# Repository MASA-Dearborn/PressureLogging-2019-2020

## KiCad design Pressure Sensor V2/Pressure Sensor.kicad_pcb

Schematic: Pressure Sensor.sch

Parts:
J1: Conn_01x10; 3M_N2510-6V0C-RB-WD
U1, U2, U3: PressureSensor; SMT-NN

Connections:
+3V3: J1.1, J1.8, U1.2, U2.2, U3.2
GND: J1.2, J1.9, U1.1, U2.1, U3.1
MISO: J1.3, U1.3, U2.3, U3.3
SCLK: J1.4, U1.4, U2.4, U3.4
SS0: J1.7, U1.5
SS1: J1.6, U2.5
SS2: J1.5, U3.5

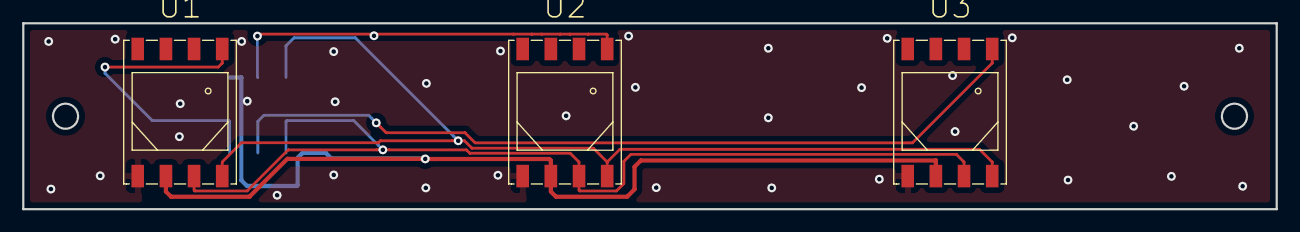
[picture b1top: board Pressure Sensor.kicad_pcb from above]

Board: 2 copper layers, 113.0 x 16.8 mm, 4 parts (1 on the bottom side), 7 nets.

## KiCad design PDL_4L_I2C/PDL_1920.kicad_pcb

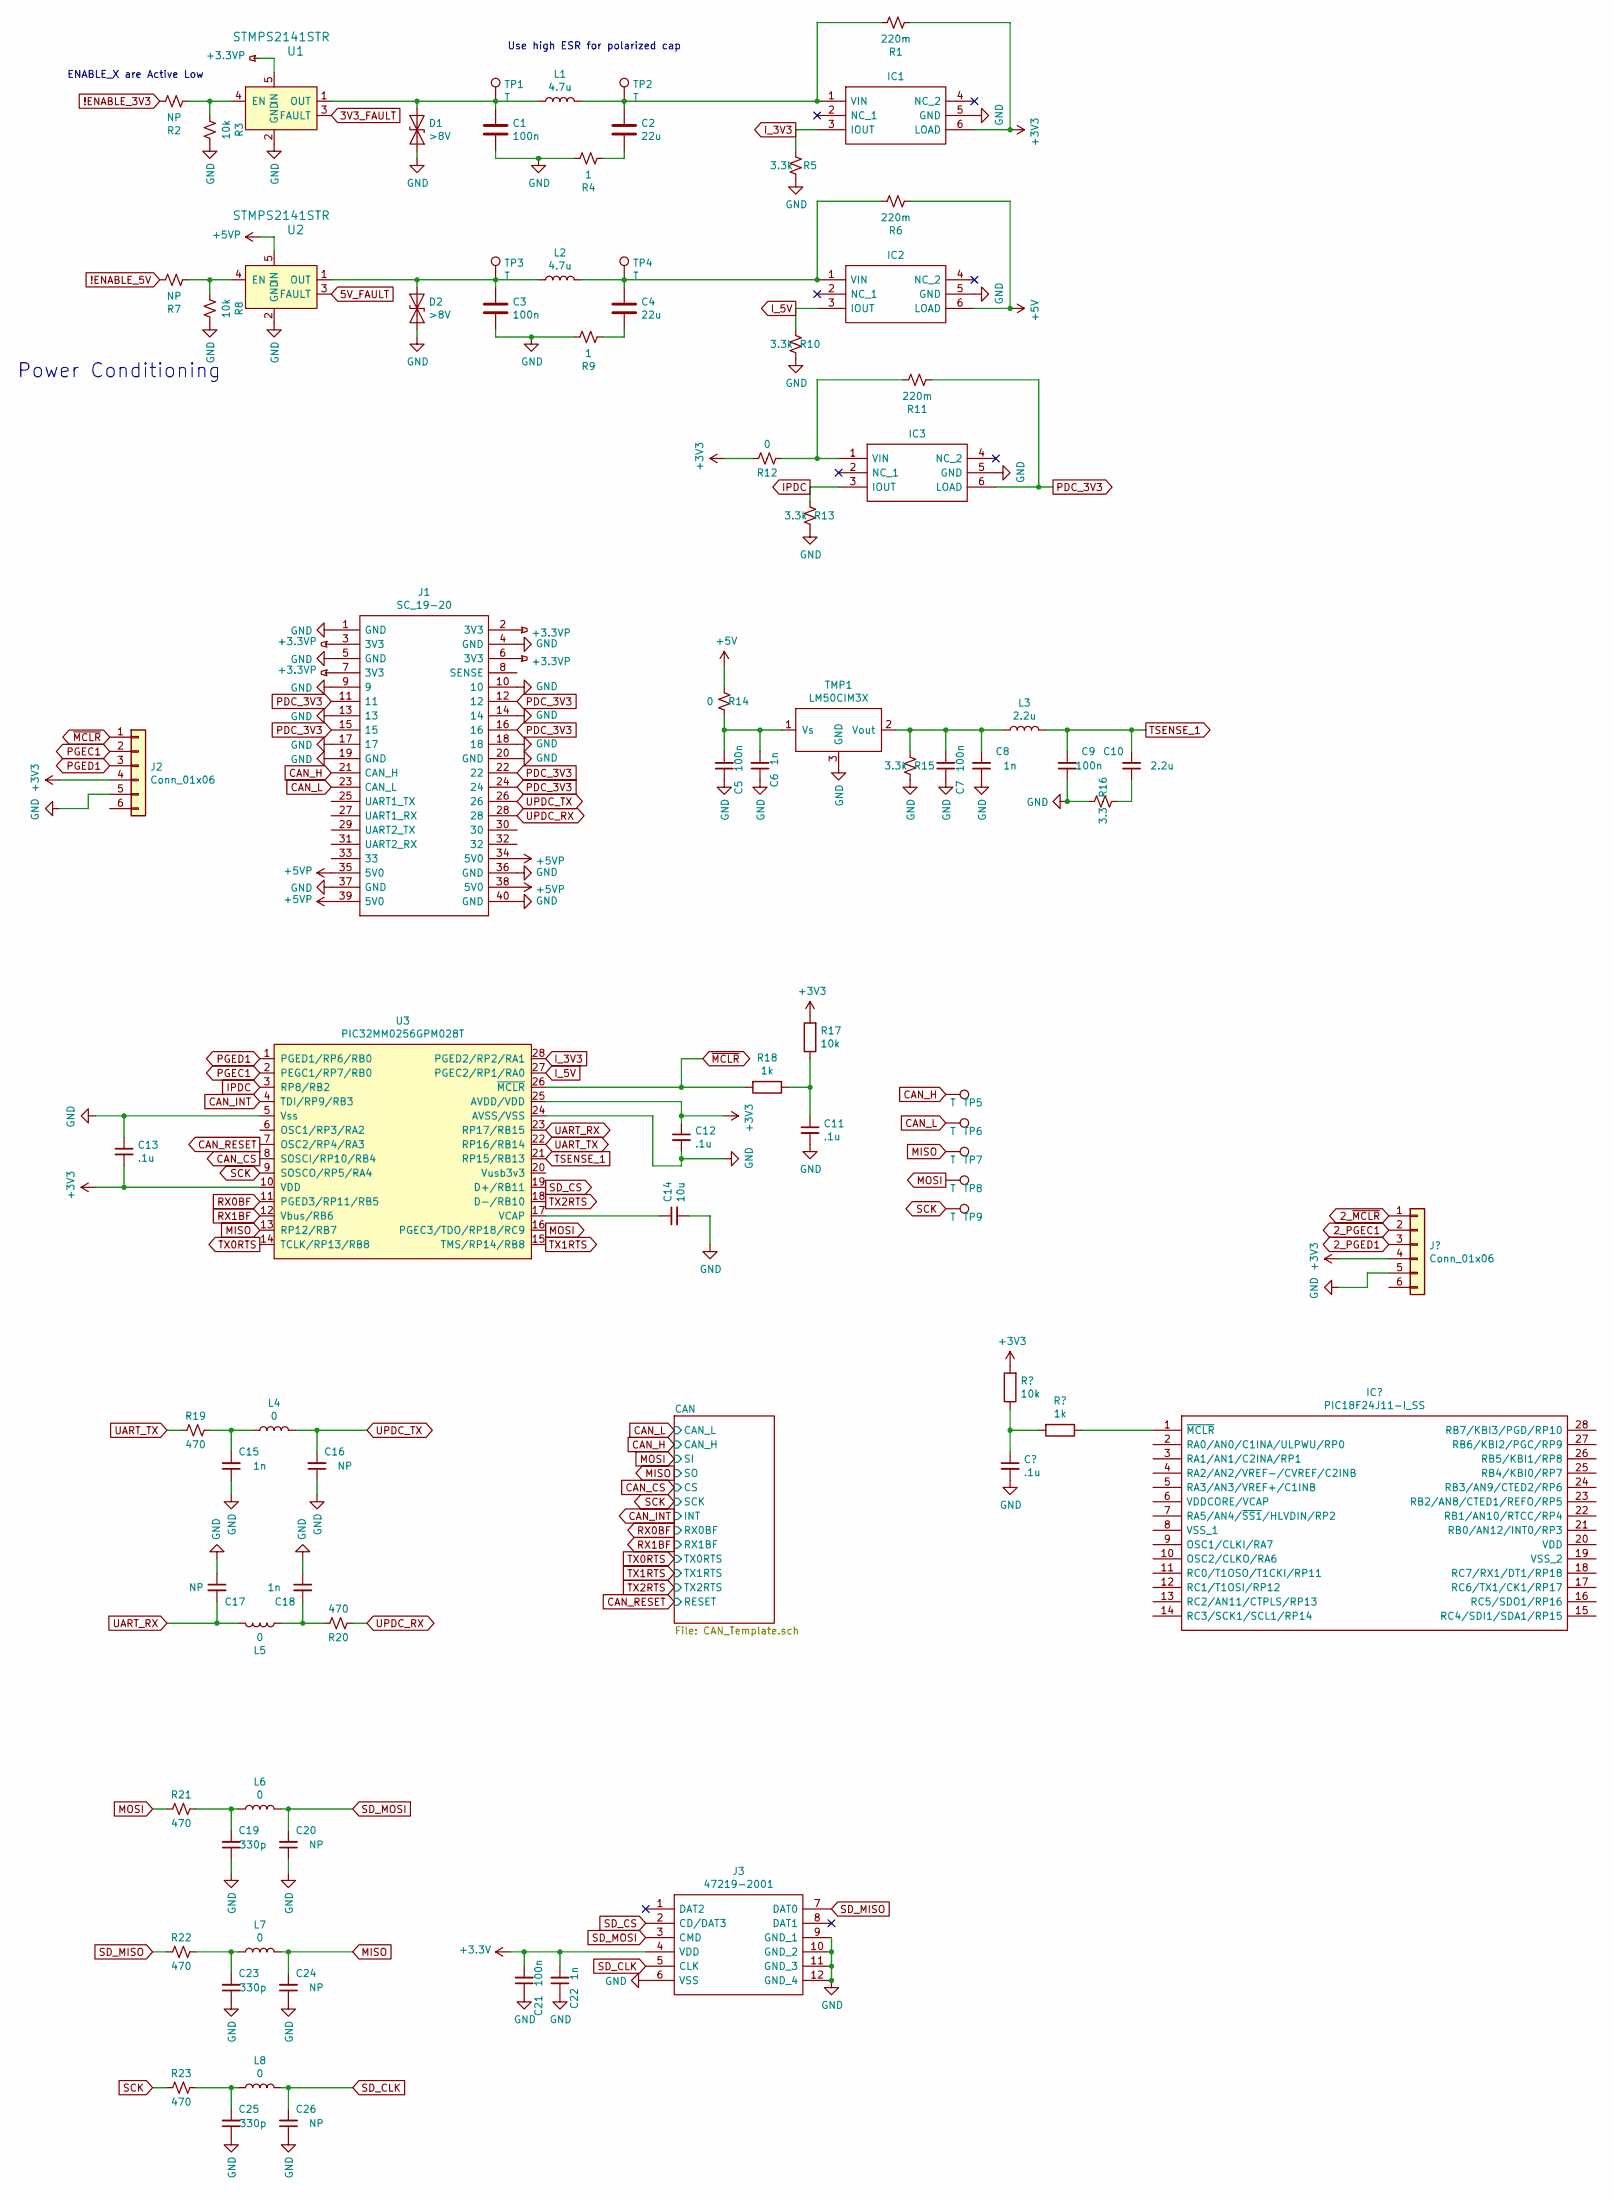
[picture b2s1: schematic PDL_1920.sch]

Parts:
C1, C3, C5, C7, C9, C21: 100n; C_0603_1608Metric
C2, C4: 22u; C_0603_1608Metric
C6, C8, C15, C18, C22: 1n; C_0603_1608Metric
C10: 2.2u; C_0603_1608Metric
C11, C12, C13: .1u; C_0603_1608Metric
C14: 10u; C_0603_1608Metric
C16, C17, C20, C24, C26: NP; C_0603_1608Metric
C19, C23, C25: 330p; C_0603_1608Metric
D1, D2: >8V; D_0805_2012Metric
IC1, IC2, IC3: FAN4010IL6X_F113; UFDFN-6_1.45x1mm; Manufacturer_Part_Number FAN4010IL6X_F113; Mouser Part Number 512-FAN4010IL6X_F113
J1: SC_19-20; Stack_Connector_2019_2020; Manufacturer_Part_Number TFC-120-32-F-D-A-K-TR
J2: Conn_01x06; PinHeader_1x06_P2.54mm_Vertical
J3: 47219-2001; 472192001; Mouser Part Number 538-47219-2001
L1: 4.7u; C_0805_2012Metric; PART# 74438324033; Digi-Key_PN 732-5684-1-ND
L2: 4.7u; L_0805_2012Metric; MPN 74438324033; Digi-Key_PN 732-5684-1-ND
L3: 2.2u; L_0603_1608Metric
L4, L5, L6, L7, L8: 0; L_0603_1608Metric
R1, R6, R11: 220m; R_0805_2012Metric
R2, R7: NP; R_0603_1608Metric
R3, R8, R17: 10k; R_0603_1608Metric
R4, R9: 1; R_0603_1608Metric
R5, R10, R13, R15: 3.3k; R_0603_1608Metric
R12, R14: 0; R_0603_1608Metric
R16: 3.3; R_0603_1608Metric
R18: 1k; R_0603_1608Metric
R19, R20, R21, R22, R23: 470; R_0603_1608Metric
TMP1: LM50CIM3X; SOT-23
TP1, TP2, TP3, TP4, TP5, TP6, TP7, TP8, TP9: T; TP380X203
U1, U2: STMPS2141STR; SOT-753; MPN STMPS2141STR; Digi-Key_PN 497-6933-1-ND
U3: PIC32MM0256GPM028T; PIC32MM0016GPL028EM6

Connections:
3V3_FAULT: U1.3 (FAULT)
5V_FAULT: U2.3 (FAULT)
!ENABLE_3V3: R2.1
!ENABLE_5V: R7.1
+3.3VP: J1.2 (3V3), J1.3 (3V3), J1.6 (3V3), J1.7 (3V3), U1.5 (IN)
+5V: IC2.6 (LOAD), R6.2, R14.2; also elsewhere on the board
+5VP: J1.34 (5V0), J1.35 (5V0), J1.38 (5V0), J1.39 (5V0), U2.5 (IN)
CAN_CS: U3.8 (SOSCI/RP10/RB4); also elsewhere on the board
CAN_H: J1.21 (CAN_H), TP5.1; also elsewhere on the board
CAN_INT: U3.4 (TDI/RP9/RB3); also elsewhere on the board
CAN_L: J1.23 (CAN_L), TP6.1; also elsewhere on the board
CAN_RESET: U3.7 (OSC2/RP4/RA3); also elsewhere on the board
IPDC: IC3.3 (IOUT), R13.2, U3.3 (RP8/RB2)
I_3V3: IC1.3 (IOUT), R5.2, U3.28 (PGED2/RP2/RA1)
I_5V: IC2.3 (IOUT), R10.2, U3.27 (PGEC2/RP1/RA0)
MISO: C24.2, L7.2, TP7.1, U3.13 (RP12/RB7); also elsewhere on the board
MOSI: R21.2, TP8.1, U3.16 (PGEC3/TDO/RP18/RC9); also elsewhere on the board
unnamed: C1.1, D1.2 (A2), L1.1, TP1.1, U1.1 (OUT)
unnamed: C2.1, IC1.1 (VIN), L1.2, R1.1, TP2.1
unnamed: C2.2, R4.2
unnamed: C3.1, D2.2 (A2), L2.1, TP3.1, U2.1 (OUT)
unnamed: C4.1, IC2.1 (VIN), L2.2, R6.1, TP4.1
unnamed: C4.2, R9.2
unnamed: C5.2, C6.2, R14.1, TMP1.1 (Vs)
unnamed: C7.2, C8.2, L3.1, R15.2, TMP1.2 (Vout)
unnamed: C10.1, R16.1
unnamed: C11.1, R17.1, R18.1
unnamed: C14.1, U3.17 (VCAP)
unnamed: C15.2, L4.1, R19.1
unnamed: C18.2, L5.1, R20.1
unnamed: C19.2, L6.1, R21.1
unnamed: C23.2, L7.1, R22.1
unnamed: C25.2, L8.1, R23.1
unnamed: IC3.1 (VIN), R11.1, R12.2
unnamed: R2.2, R3.2, U1.4 (EN)
unnamed: R7.2, R8.2, U2.4 (EN)
PDC_3V3: IC3.6 (LOAD), J1.11, J1.12, J1.15, J1.16, J1.22, J1.24, R11.2
PGEC1: J2.2, U3.2 (PEGC1/RP7/RB0)
PGED1: J2.3, U3.1 (PGED1/RP6/RB0)
RX0BF: U3.11 (PGED3/RP11/RB5); also elsewhere on the board
RX1BF: U3.12 (Vbus/RB6); also elsewhere on the board
SCK: R23.2, TP9.1, U3.9 (SOSCO/RP5/RA4); also elsewhere on the board
SD_CLK: C26.2, J3.5 (CLK), L8.2
SD_CS: J3.2 (CD/DAT3), U3.19 (D+/RB11)
SD_MISO: J3.7 (DAT0), R22.2
SD_MOSI: C20.2, J3.3 (CMD), L6.2
TSENSE_1: C9.2, C10.2, L3.2, U3.21 (RP15/RB13)
TX0RTS: U3.14 (TCLK/RP13/RB8); also elsewhere on the board
TX1RTS: U3.15 (TMS/RP14/RB8); also elsewhere on the board
TX2RTS: U3.18 (D-/RB10); also elsewhere on the board
UART_RX: C17.2, L5.2, U3.23 (RP17/RB15)
UART_TX: R19.2, U3.22 (RP16/RB14)
UPDC_RX: J1.28, R20.2
UPDC_TX: C16.2, J1.26, L4.2
~MCLR: J2.1, R18.2, U3.26 (~MCLR)

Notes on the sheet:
Use high ESR for polarized cap
ENABLE_X are Active Low
Power Conditioning

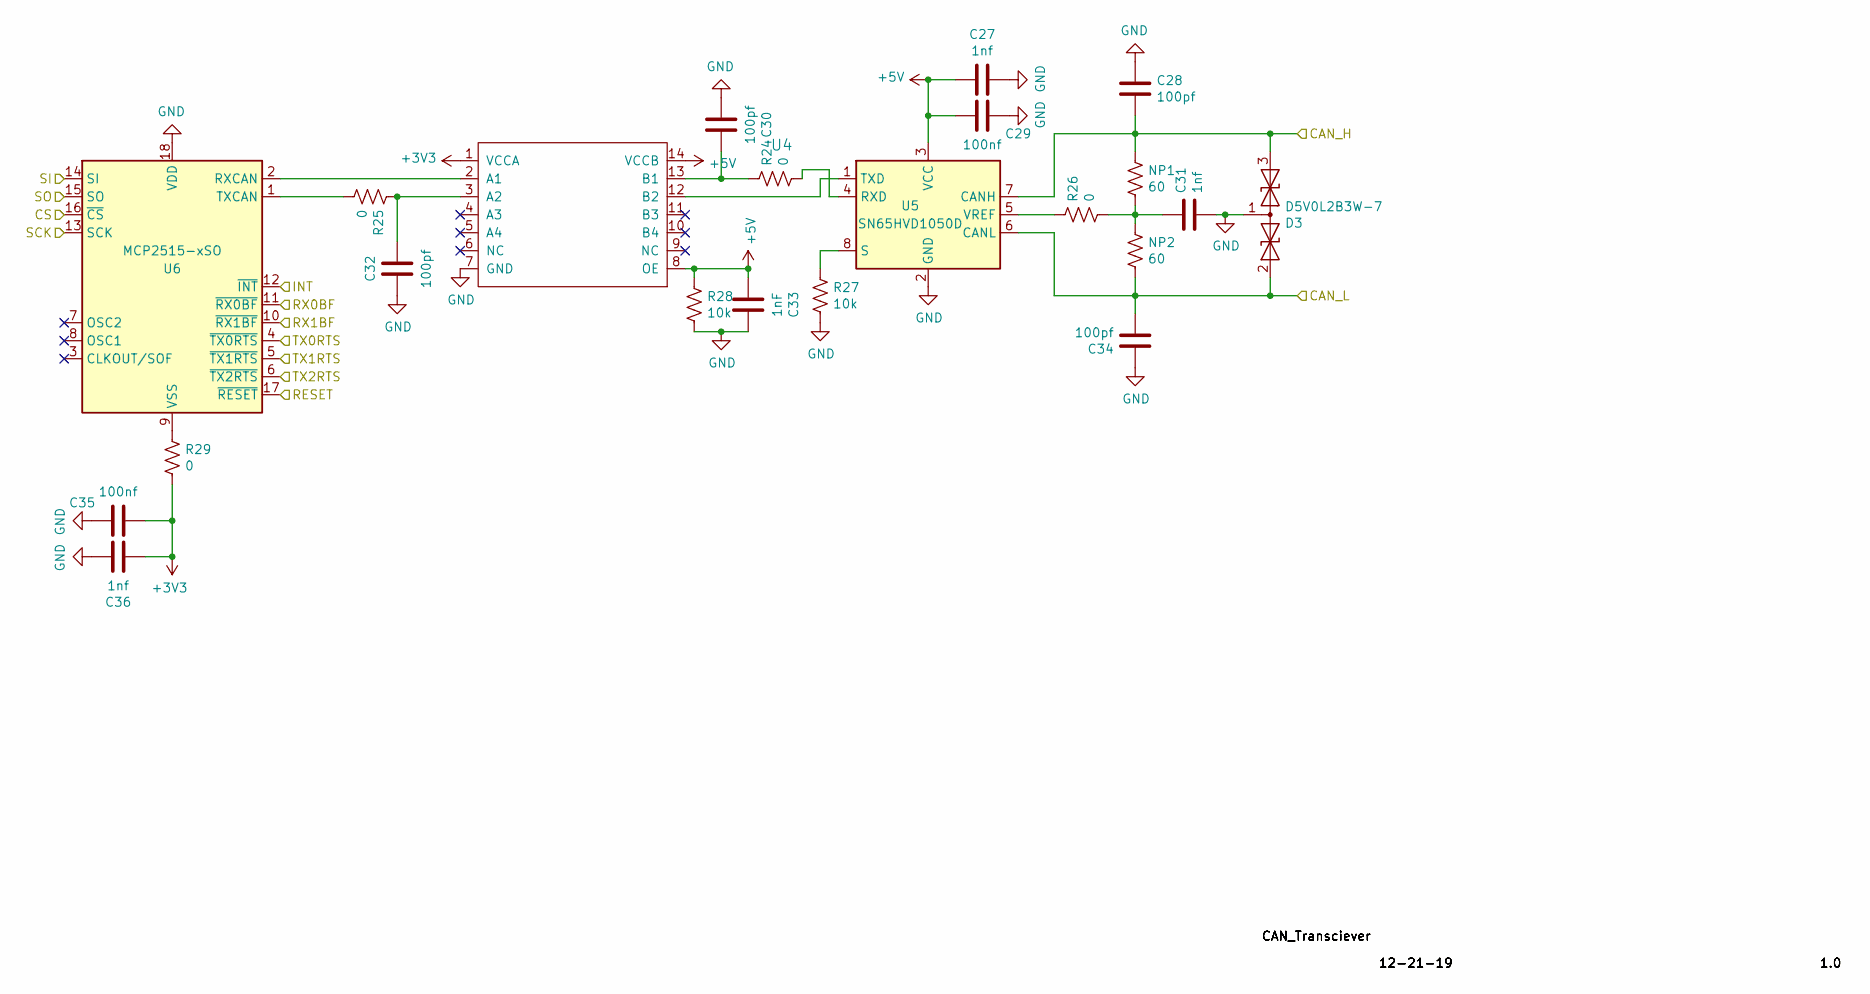
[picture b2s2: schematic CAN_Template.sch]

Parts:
C27, C31, C36: 1nf; C_0603_1608Metric
C28, C30, C32, C34: 100pf; C_0603_1608Metric
C29, C35: 100nf; C_0603_1608Metric
C33: 1nF; C_0603_1608Metric
D3: D5V0L2B3W-7; SOT-23
NP1, NP2: 60; R_0603_1608Metric
R24, R25, R26, R29: 0; R_0603_1608Metric
R27, R28: 10k; R_0603_1608Metric
U4: TXB0104PWR
U5: SN65HVD1050D; SOIC-8_3.9x4.9mm_P1.27mm
U6: MCP2515-xSO; SOIC-18W_7.5x11.6mm_P1.27mm

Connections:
+5V: C27.2, C29.1, C33.2, R28.1, U4.8 (OE), U4.14 (VCCB), U5.3 (VCC); also elsewhere on the board
CAN_CS: U6.16 (~CS); also elsewhere on the board
CAN_H: C28.2, D3.3 (A2), NP1.1, U5.7 (CANH); also elsewhere on the board
CAN_INT: U6.12 (~INT); also elsewhere on the board
CAN_L: C34.2, D3.2 (A1), NP2.2, U5.6 (CANL); also elsewhere on the board
CAN_RESET: U6.17 (~RESET); also elsewhere on the board
MISO: U6.15 (SO); also elsewhere on the board
MOSI: U6.14 (SI); also elsewhere on the board
unnamed: C30.1, R24.1, U4.13 (B1)
unnamed: C31.1, NP1.2, NP2.1, R26.2
unnamed: C32.2, R25.1, U4.3 (A2)
unnamed: R24.2, U5.4 (RXD)
unnamed: R25.2, U6.1 (TXCAN)
unnamed: R26.1, U5.5 (VREF)
unnamed: R27.1, U5.8 (S)
unnamed: R29.1, U6.9 (VSS)
unnamed: U4.2 (A1), U6.2 (RXCAN)
unnamed: U4.12 (B2), U5.1 (TXD)
RX0BF: U6.11 (~RX0BF); also elsewhere on the board
RX1BF: U6.10 (~RX1BF); also elsewhere on the board
SCK: U6.13 (SCK); also elsewhere on the board
TX0RTS: U6.4 (~TX0RTS); also elsewhere on the board
TX1RTS: U6.5 (~TX1RTS); also elsewhere on the board
TX2RTS: U6.6 (~TX2RTS); also elsewhere on the board

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
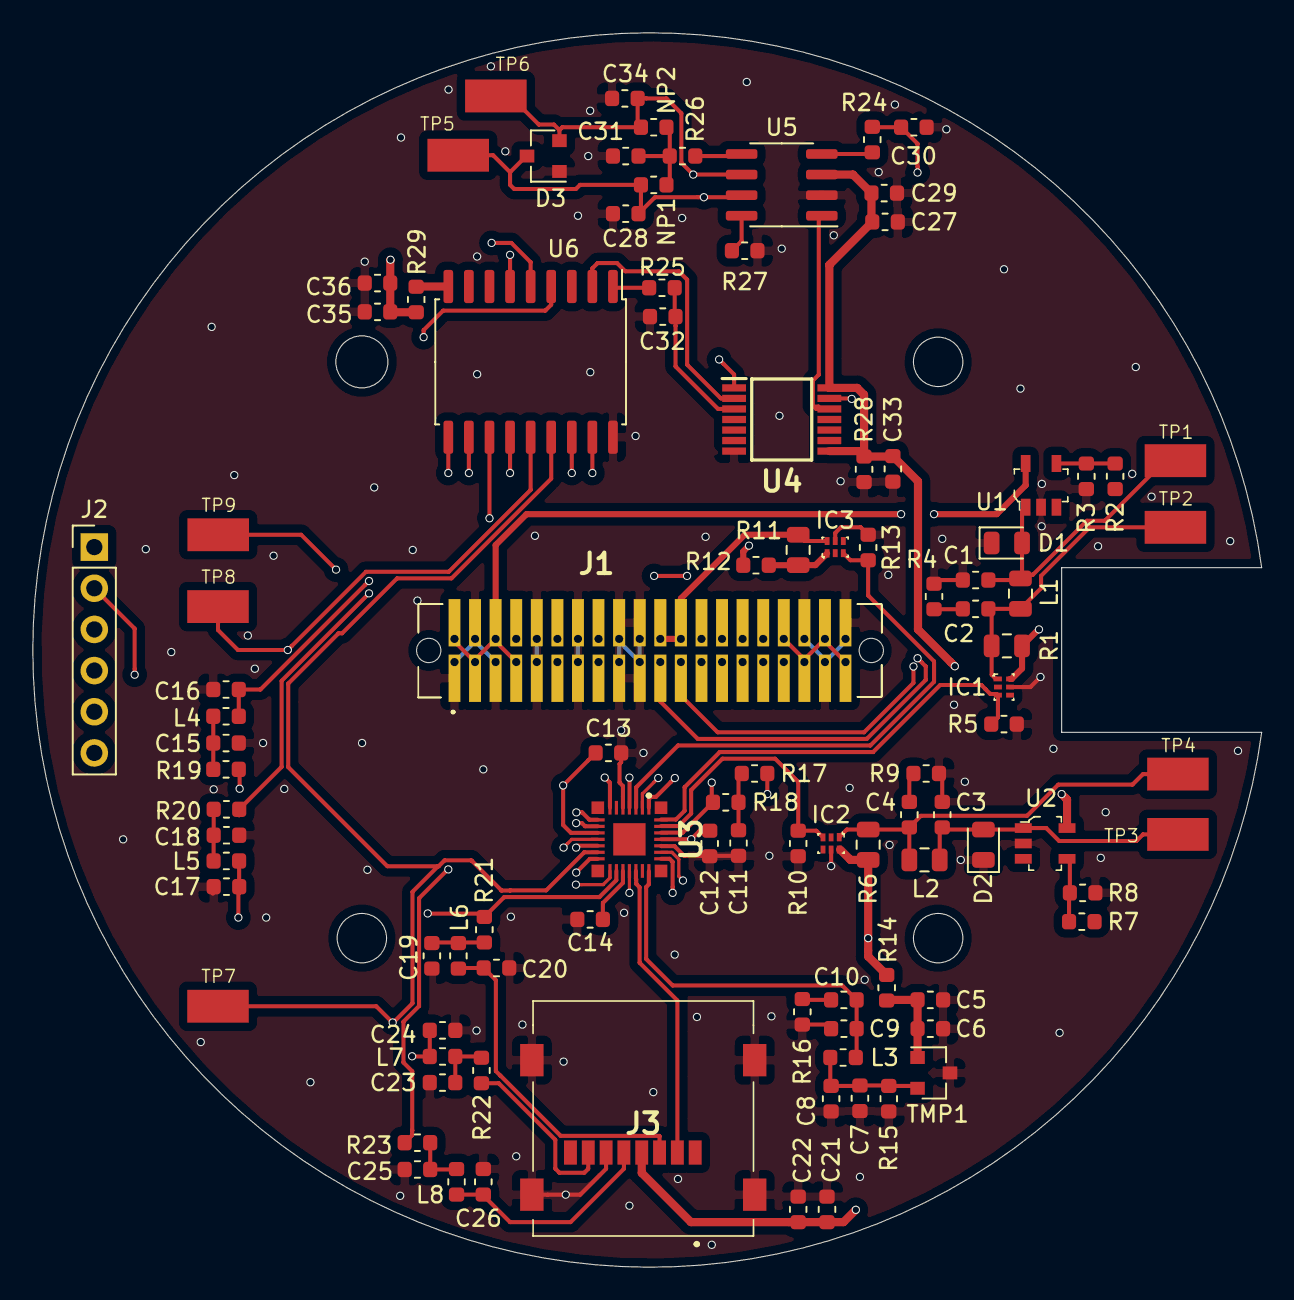
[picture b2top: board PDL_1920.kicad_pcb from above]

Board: 4 copper layers, 75.8 x 76.2 mm, 100 parts (0 on the bottom side), 63 nets.

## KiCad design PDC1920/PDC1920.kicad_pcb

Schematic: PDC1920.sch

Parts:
C1, C2: .1u; C_0603_1608Metric_Pad1.05x0.95mm_HandSolder
C3, C6: 1n; C_0603_1608Metric_Pad1.05x0.95mm_HandSolder
C4, C5: NP; C_0603_1608Metric_Pad1.05x0.95mm_HandSolder
IC1: PIC16LF1826-I_SO; SOIC127P1030X265-18N; Mouser Part Number 579-PIC16LF1826-I/SO
IC2: LM60CIM3_NOPB; SOT95P237X112-3N; Mouser Part Number 926-LM60CIM3/NOPB
J1: Conn_01x04; 37946364
J2: Conn_01x06; PinHeader_1x06_P2.54mm_Vertical_SMD_Pin1Right
J3: Conn_01x10_Male; 3M_N2510-6V0C-RB-WD
L1, L2: 0; L_0603_1608Metric_Pad1.05x0.95mm_HandSolder
R1: 10k; R_0603_1608Metric_Pad1.05x0.95mm_HandSolder
R2: 1k; R_0603_1608Metric_Pad1.05x0.95mm_HandSolder
R3, R4: 470; R_0603_1608Metric_Pad1.05x0.95mm_HandSolder
U1, U2, U3: PressureSensor

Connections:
+3V3: C2.1, IC1.14 (VDD), IC2.1 (VS+), J1.1, J2.4, J3.1, J3.8, R1.2, U1.2, U2.2, U3.2
GND: C1.2, C2.2, C3.2, C4.2, C5.2, C6.2, IC1.5 (VSS), IC2.3 (GND), J1.2, J2.5, J3.2, J3.9, U1.1, U2.1, U3.1
ICSPCLK: IC1.12 (RB6), J2.2
ICSPDAT: IC1.13 (RB7), J2.3
MISO: IC1.7 (RB1), J3.3, U1.3, U2.3, U3.3
unnamed: C1.1, R1.1, R2.2
unnamed: C3.1, L1.1, R3.2
unnamed: C6.1, L2.2, R4.1
RX_Pic: IC1.8 (RB2), R4.2
SCLK: IC1.10 (RB4), J3.4, U1.4, U2.4, U3.4
SS0: IC1.1 (RA2), J3.7
SS1: IC1.2 (RA3), J3.6
SS2: IC1.3 (RA4), J3.5
SS3: IC1.15 (RA6), U1.5
SS4: IC1.16 (RA7), U2.5
SS5: IC1.17 (RA0), U3.5
TX_Pic: C5.1, IC1.11 (RB5), L1.2
TempO: IC1.18 (RA1), IC2.2 (V0)
UART_RX: C4.1, J1.4, L2.1
UART_TX: J1.3, R3.1
~MCLR: IC1.4 (RA5/~MCLR~/VPP), J2.1, R2.1

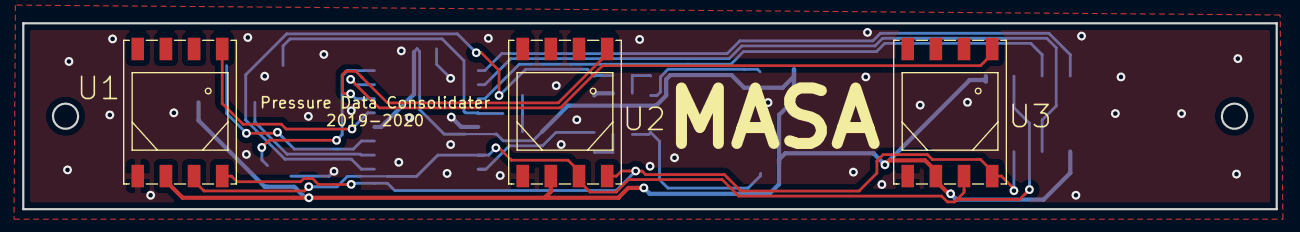
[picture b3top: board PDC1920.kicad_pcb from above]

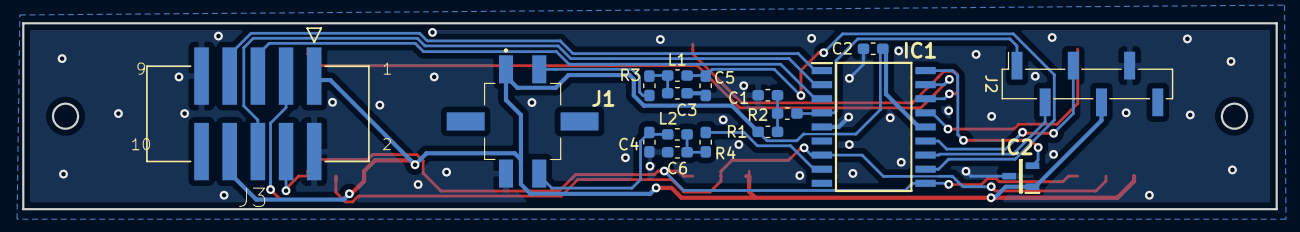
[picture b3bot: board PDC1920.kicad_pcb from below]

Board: 2 copper layers, 113.0 x 16.8 mm, 20 parts (17 on the bottom side), 21 nets.

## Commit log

2020-01-09 First commit of files
2020-01-09 Pressure Sensor Board
2020-01-14 New thing
2020-01-26 Added PDL
2020-01-26 PDC updates
2020-01-30 Pressure Sensor V2
2020-02-19 Clearance changes
